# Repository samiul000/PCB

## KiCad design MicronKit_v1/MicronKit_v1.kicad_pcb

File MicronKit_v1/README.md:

<div align="center">
<h1>MicronKit : PIC32 based MCU Program Flasher (V1.0)</h1>

</div>

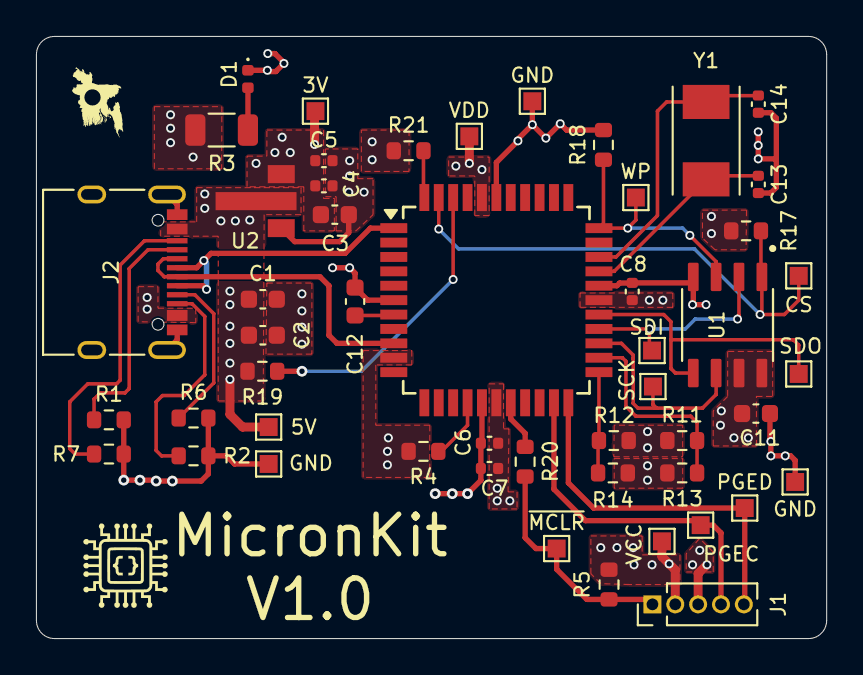
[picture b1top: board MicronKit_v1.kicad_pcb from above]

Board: 4 copper layers, 43.9 x 33.4 mm, 49 parts (0 on the bottom side), 27 nets.

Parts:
3V, 5V: TestPoint; TestPoint_Pad_1.0x1.0mm
C1: 0.22uF; C_0603_1608Metric
C2, C3, C11: 1uF; C_0603_1608Metric
C4, C6, C7, C8: 0.1uF; C_0402_1005Metric
C5: 10nF; C_0402_1005Metric
C12: 10uF; C_0603_1608Metric
C13, C14: 22pF; C_0402_1005Metric
CS: TestPoint; TestPoint_Pad_1.0x1.0mm
D1: LED; LED_0402_1005Metric
GND: TestPoint; TestPoint_Pad_1.0x1.0mm
GND#2, GND#3: TestPoint; TestPoint_Pad_1.0x1.0mm
J1: Conn_01x05_Pin; PinHeader_1x05_P1.27mm_Vertical
J2: USB_C_Receptacle_USB2.0_16P; USB_C_Receptacle_XKB_U262-16XN-4BVC11
PGEC: TestPoint; TestPoint_Pad_1.0x1.0mm
PGED: TestPoint; TestPoint_Pad_1.0x1.0mm
R1, R2, R6, R7: 5.1K; R_0603_1608Metric
R3: 1K; R_1206_3216Metric
R4, R5, R12, R17, R21: 10K; R_0603_1608Metric
R11: 3.92K; R_0603_1608Metric
R13, R14: 2.21K; R_0603_1608Metric
R18: 2.2K; R_0603_1608Metric
R19: 100; R_0603_1608Metric
R20: 470; R_0603_1608Metric
SCK: TestPoint; TestPoint_Pad_1.0x1.0mm
SDI: TestPoint; TestPoint_Pad_1.0x1.0mm
SDO: TestPoint; TestPoint_Pad_1.0x1.0mm
U1: 25LC256; 25LC256-I_SN
U2: MCP1700T-3302E_MB
U3: PIC32MX250F128D-IPT; TQFP-44_10x10mm_P0.8mm
VCC: TestPoint; TestPoint_Pad_1.0x1.0mm
VDD: TestPoint; TestPoint_Pad_1.0x1.0mm
WP: TestPoint; TestPoint_Pad_1.0x1.0mm
Y1: 12 MHz; Crystal_SMD_Abracon_ABM7-2Pin_6.0x3.5mm

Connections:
+3.3V: 3V.1, C3.1, C4.1, C5.1, C6.1, C7.1, C8.1, C11.1, J1.2, R3.1, R4.1, R5.1, R11.1, R12.1, R17.1, R21.1, U1.7 (~HOLD), U1.8 (VDD), U2.3 (VO), U3.10 (VUSB3V3), U3.17 (AVDD), U3.28 (VDD), U3.40 (VDD), VCC.1, VDD.1
+5V: 5V.1, C1.1, C2.1, J2.A4 (VBUS), J2.A9 (VBUS), J2.B4 (VBUS), J2.B9 (VBUS), R19.2, U2.2 (VI)
A5: J2.A5 (CC1), R1.1
A8: J2.A8 (SBU1), R6.1
B5: J2.B5 (CC2), R2.1
B8: J2.B8 (SBU2), R7.1
D_Minus: J2.A7 (D-), J2.B7 (D-), U3.9 (RB11)
D_Plus: J2.A6 (D+), J2.B6 (D+), U3.1 (RB9)
GND: C1.2, C2.2, C3.2, C4.2, C5.2, C6.2, C7.2, C8.2, C11.2, C12.1, C13.2, C14.2, D1.1 (K), GND.1, GND#2.1, GND#3.1, J1.3, J2.A1 (GND), J2.A12 (GND), J2.B1 (GND), J2.B12 (GND), J2.S1 (SHIELD), R1.2, R2.2, R6.2, R7.2, R13.2, R14.2, R18.2, U1.4 (GND), U2.1 (GND), U3.6 (VSS), U3.16 (AVSS), U3.29 (VSS), U3.39 (VSS)
unnamed: D1.2 (A), R3.2
unnamed: C13.1, U3.30 (RA2), Y1.1
unnamed: C14.1, U3.31 (RA3), Y1.2
unnamed: R21.2, U3.44 (RB8)
unnamed: R19.1, U3.42 (VBUS)
unnamed: C12.2, U3.7 (VCAP)
unnamed: R20.2, U3.18 (~MCLR)
PGEC: J1.4, PGEC.1, U3.21 (RB0)
PGED: J1.5, PGED.1, U3.22 (RB1)
Power_Good: R4.2, U3.15 (RB15)
UTIL_CS: CS.1, R17.2, U1.1 (~CS), U3.43 (RB7)
UTIL_SCK: SCK.1, U1.6 (SCK), U3.25 (RC0)
UTIL_SDI: SDI.1, U1.2 (SDO), U3.26 (RC1)
UTIL_SDO: SDO.1, U1.5 (SDI), U3.27 (RC2)
UTIL_WP: R18.1, U1.3 (~WP), U3.33 (RB4), WP.1
VDD_SENSE: R11.2, R13.1, U3.24 (RB3)
VPP_SENSE: R12.2, R14.1, U3.23 (RB2)
~MCLR: J1.1, R5.2, R20.1

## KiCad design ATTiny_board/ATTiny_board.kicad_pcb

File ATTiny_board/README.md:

<div align="center">
<h1>Tiny Board: ATTiny87-M based dev board</h1>

</div>

---

## Hardware
- Flash Program Memory:	8 KB
- SRAM (RAM):	512 bytes
- EEPROM:	512 bytes
- Maximum Clock Speed:	16 MHz
- CPU Architecture:	AVR 8-bit RISC
- GPIO Pins: 10
- I2C: 1
- SPI: 1
- Dimension: 26.75mm x 28.025mm

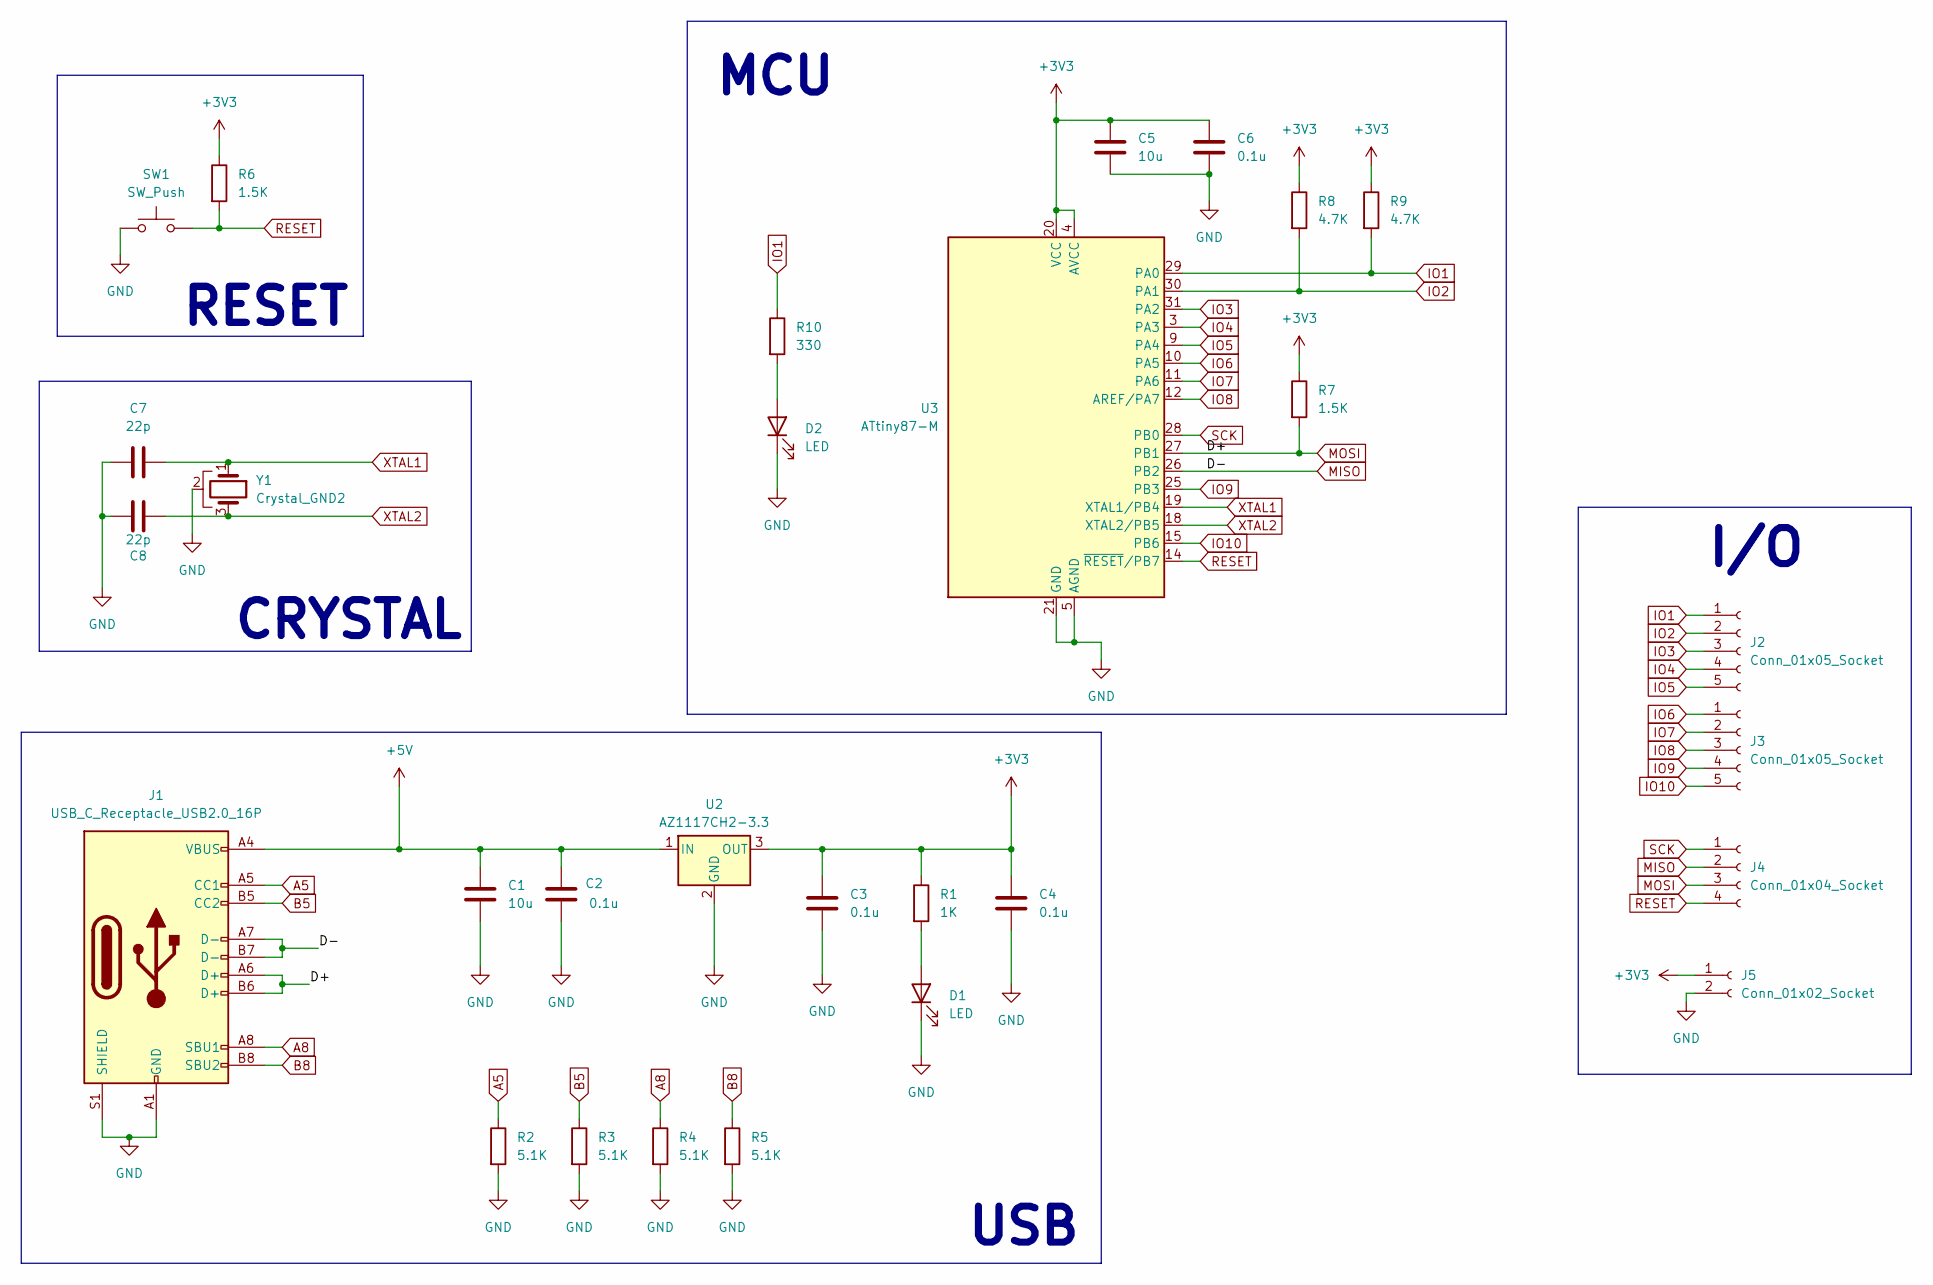
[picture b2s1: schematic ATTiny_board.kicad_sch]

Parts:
C1, C5: 10u; C_0603_1608Metric
C2, C3, C4, C6: 0.1u; C_0603_1608Metric
C7, C8: 22p; C_0402_1005Metric
D1, D2: LED; LED_0603_1608Metric
J1: USB_C_Receptacle_USB2.0_16P; USB_C_Receptacle_GCT_USB4105-xx-A_16P_TopMnt_Horizontal
J2, J3: Conn_01x05_Socket; PinSocket_1x05_P2.54mm_Vertical
J4: Conn_01x04_Socket; PinSocket_1x04_P2.54mm_Vertical
J5: Conn_01x02_Socket; PinSocket_1x02_P2.54mm_Vertical
R1: 1K; R_0603_1608Metric
R2, R3, R4, R5: 5.1K; R_0603_1608Metric
R6, R7: 1.5K; R_0603_1608Metric
R8, R9: 4.7K; R_0603_1608Metric
R10: 330; R_0603_1608Metric
SW1: SW_Push; SW_Push_1P1T_NO_CK_KMR2
U2: AZ1117CH2-3.3; SOT-223-3_TabPin2
U3: ATtiny87-M; QFN-32-1EP_5x5mm_P0.5mm_EP3.1x3.1mm
Y1: Crystal_GND2; XTAL_C3E-12.000-18-3030-X-R

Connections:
+3V3: C3.1, C4.1, C5.1, C6.1, J5.1, R1.1, R6.1, R7.1, R8.1, R9.1, U2.3 (OUT), U3.4 (AVCC), U3.20 (VCC)
+5V: C1.1, C2.1, J1.A4 (VBUS), J1.A9 (VBUS), J1.B4 (VBUS), J1.B9 (VBUS), U2.1 (IN)
A5: J1.A5 (CC1), R2.1
A8: J1.A8 (SBU1), R4.1
B5: J1.B5 (CC2), R3.1
B8: J1.B8 (SBU2), R5.1
GND: C1.2, C2.2, C3.2, C4.2, C5.2, C6.2, C7.1, C8.2, D1.1 (K), D2.1 (K), J1.A1 (GND), J1.A12 (GND), J1.B1 (GND), J1.B12 (GND), J1.S1 (SHIELD), J5.2, R2.2, R3.2, R4.2, R5.2, SW1.1, U2.2 (GND), U3.5 (AGND), U3.21 (GND), U3.33 (GND), Y1.2
IO1: J2.1, R9.2, R10.1, U3.29 (PA0)
IO2: J2.2, R8.2, U3.30 (PA1)
IO3: J2.3, U3.31 (PA2)
IO4: J2.4, U3.3 (PA3)
IO5: J2.5, U3.9 (PA4)
IO6: J3.1, U3.10 (PA5)
IO7: J3.2, U3.11 (PA6)
IO8: J3.3, U3.12 (AREF/PA7)
IO9: J3.4, U3.25 (PB3)
IO10: J3.5, U3.15 (PB6)
MISO: J1.A7 (D-), J1.B7 (D-), J4.2, U3.26 (PB2)
MOSI: J1.A6 (D+), J1.B6 (D+), J4.3, R7.2, U3.27 (PB1)
unnamed: D1.2 (A), R1.2
unnamed: D2.2 (A), R10.2
RESET: J4.4, R6.2, SW1.2, U3.14 (~RESET/PB7)
SCK: J4.1, U3.28 (PB0)
XTAL1: C7.2, U3.19 (XTAL1/PB4), Y1.1
XTAL2: C8.1, U3.18 (XTAL2/PB5), Y1.3

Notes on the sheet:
I/O
CRYSTAL
USB
MCU
RESET

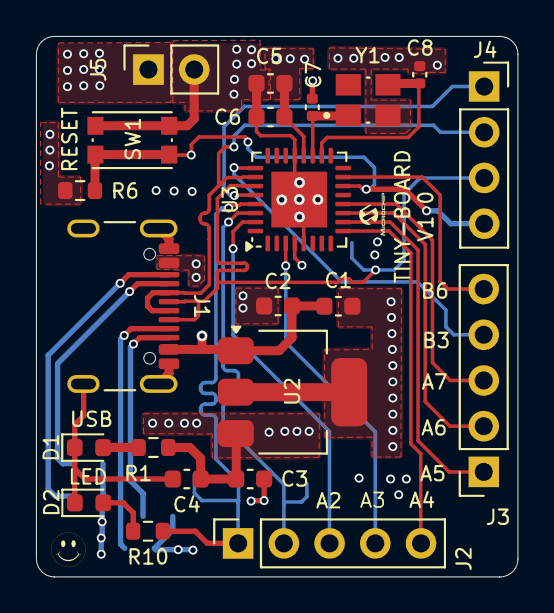
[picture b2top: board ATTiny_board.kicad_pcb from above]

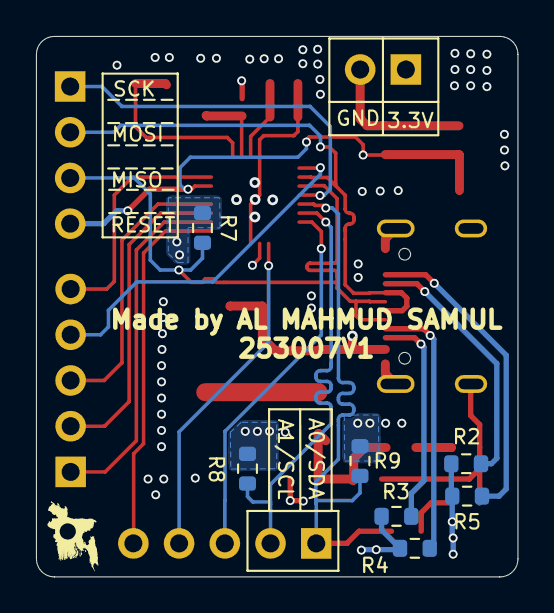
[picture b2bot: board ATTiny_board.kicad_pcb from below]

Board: 4 copper layers, 26.8 x 30.0 mm, 29 parts (7 on the bottom side), 25 nets.

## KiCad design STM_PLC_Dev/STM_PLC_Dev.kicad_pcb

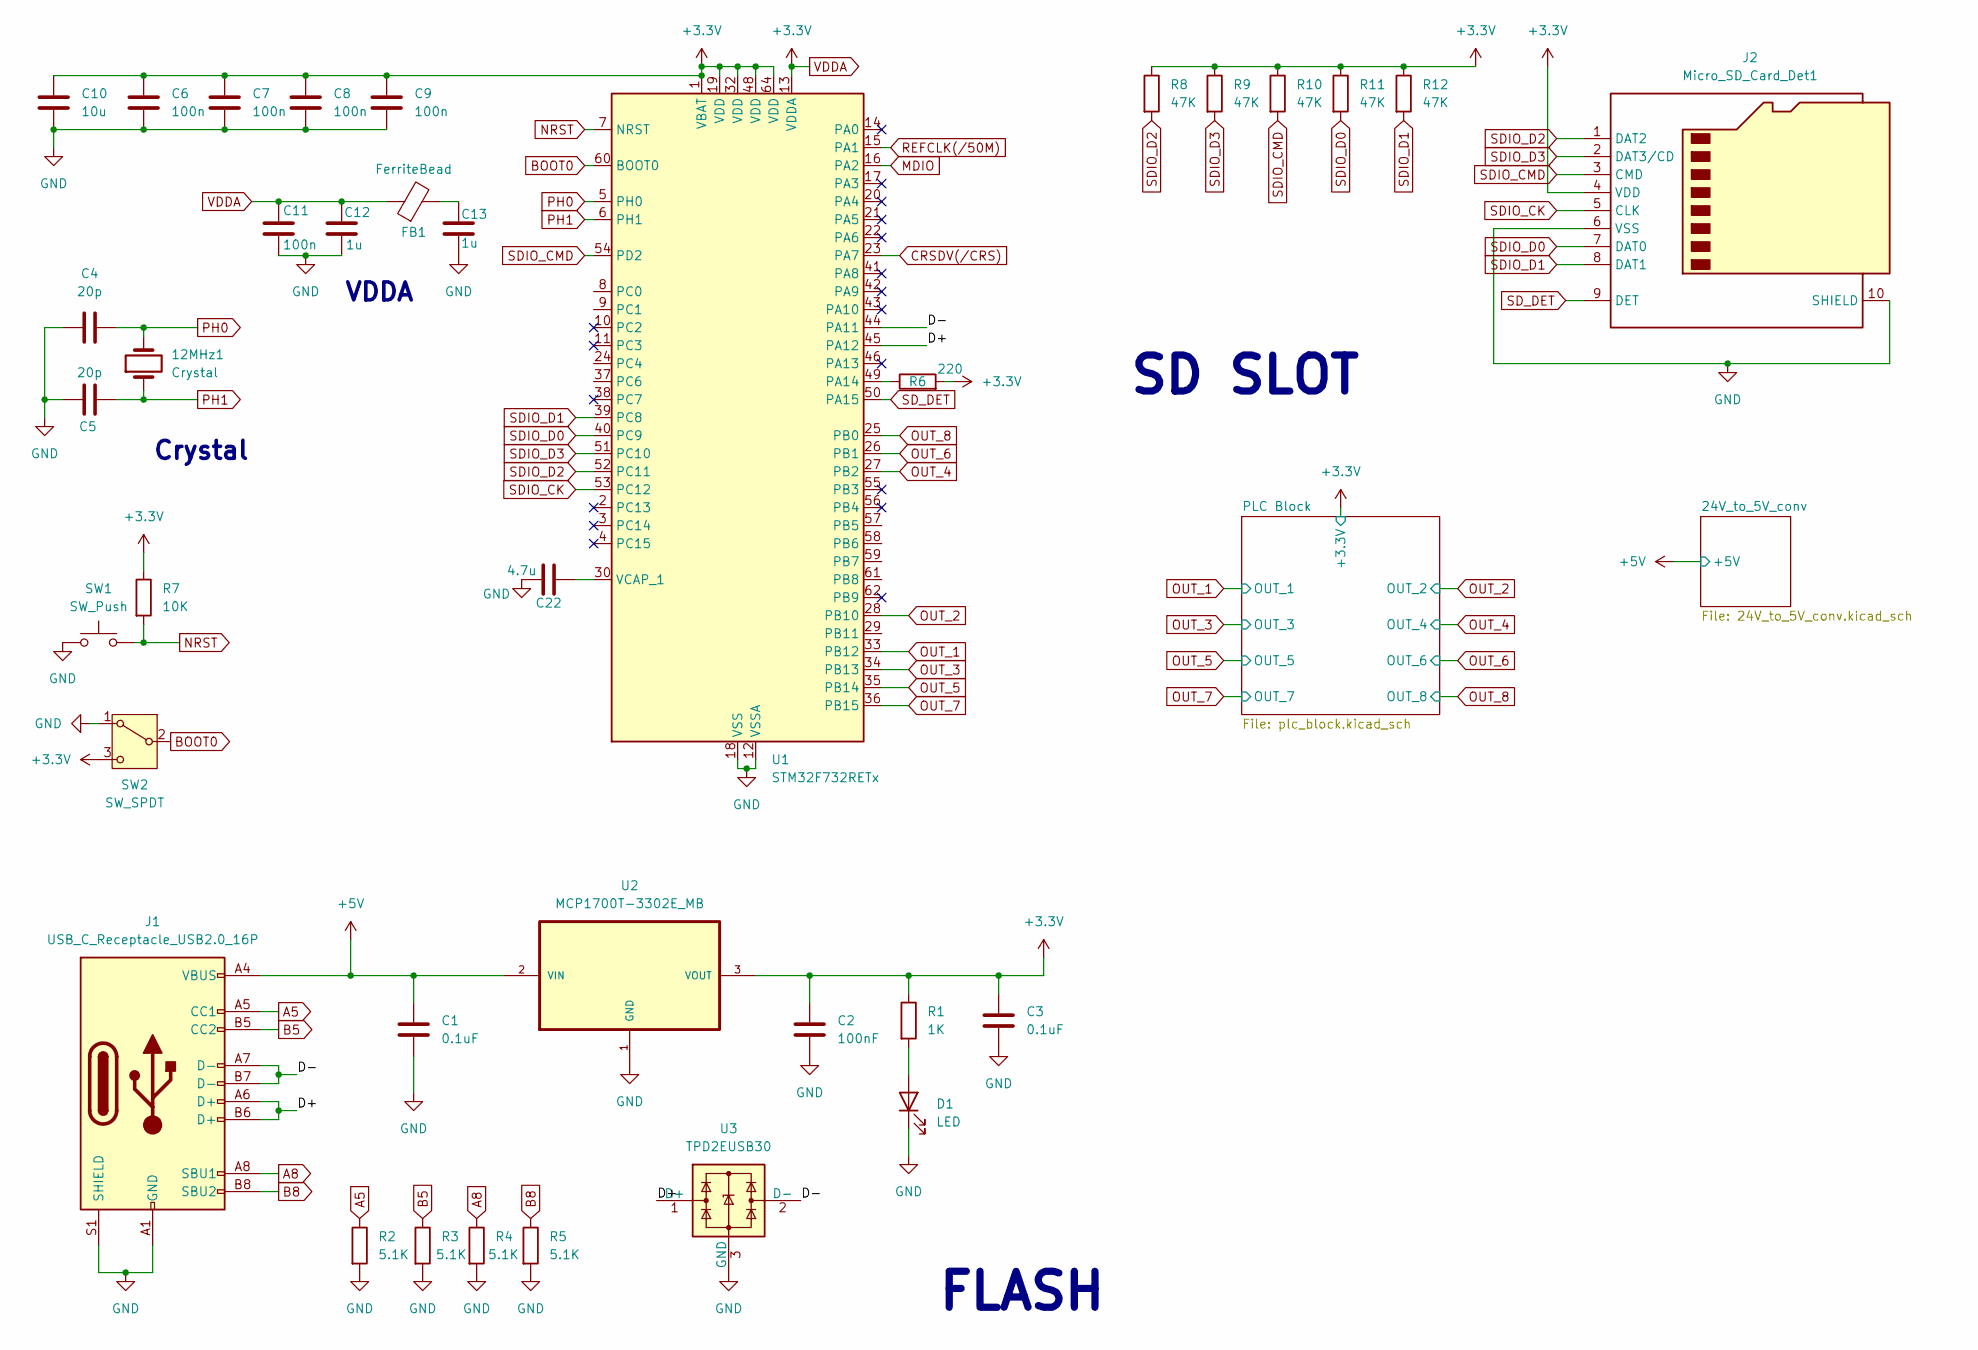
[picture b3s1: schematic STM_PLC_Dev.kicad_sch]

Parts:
12MHz1: Crystal; XTAL_HC49P488W46L1150T500H350
C1, C3: 0.1uF; C_0603_1608Metric
C2: 100nF; C_0603_1608Metric
C4, C5: 20p; C_0603_1608Metric
C6, C7, C8, C9, C11: 100n; C_0603_1608Metric
C10: 10u; C_0603_1608Metric
C12, C13: 1u; C_0603_1608Metric
C22: 4.7u; C_0603_1608Metric
D1: LED; LED_0805_2012Metric
FB1: FerriteBead; LairdTech_28C0236-0JW-10
J1: USB_C_Receptacle_USB2.0_16P; USB_C_Receptacle_G-Switch_GT-USB-7010ASV
J2: Micro_SD_Card_Det1; microSD_HC_Hirose_DM3AT-SF-PEJM5
R1: 1K; R_0805_2012Metric
R2, R3, R4, R5: 5.1K; R_0805_2012Metric
R6: 220; R_0603_1608Metric
R7: 10K; R_0805_2012Metric
R8, R9, R10, R11, R12: 47K; R_0805_2012Metric
SW1: SW_Push; SW_PUSH-12mm_Wuerth-430476085716
SW2: SW_SPDT; SW_E-Switch_EG1224_SPDT_Angled
U1: STM32F732RETx; LQFP-64_10x10mm_P0.5mm
U2: MCP1700T-3302E_MB
U3: TPD2EUSB30; Texas_DRT-3

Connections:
+5V: C1.1, J1.A4 (VBUS), J1.A9 (VBUS), J1.B4 (VBUS), J1.B9 (VBUS), U2.2 (VIN); also elsewhere on the board
/D+: J1.A6 (D+), J1.B6 (D+), U1.45 (PA12), U3.1 (D+)
/D-: J1.A7 (D-), J1.B7 (D-), U1.44 (PA11), U3.2 (D-)
A5: J1.A5 (CC1), R2.1
A8: J1.A8 (SBU1), R4.1
B5: J1.B5 (CC2), R3.1
B8: J1.B8 (SBU2), R5.1
BOOT0: SW2.2 (B), U1.60 (BOOT0)
CRSDV(/CRS): U1.23 (PA7)
GND: C1.2, C2.2, C3.2, C4.1, C5.1, C6.2, C7.2, C8.2, C9.2, C10.2, C11.2, C12.2, C13.2, C22.1, D1.1 (K), J1.A1 (GND), J1.A12 (GND), J1.B1 (GND), J1.B12 (GND), J1.S1 (SHIELD), J2.6 (VSS), J2.10 (SHIELD), R2.2, R3.2, R4.2, R5.2, SW1.1, SW2.1 (A), U1.12 (VSSA), U1.18 (VSS), U1.31 (VSS), U1.47 (VSS), U1.63 (VSS), U2.1 (GND), U3.3 (GND); also elsewhere on the board
MDIO: U1.16 (PA2)
NRST: R7.2, SW1.2, U1.7 (NRST)
unnamed: C13.1, FB1.2
unnamed: D1.2 (A), R1.2
unnamed: R6.1, U1.49 (PA14)
unnamed: C22.2, U1.30 (VCAP_1)
OUT_1: U1.33 (PB12); also elsewhere on the board
OUT_2: U1.28 (PB10); also elsewhere on the board
OUT_3: U1.34 (PB13); also elsewhere on the board
OUT_4: U1.27 (PB2); also elsewhere on the board
OUT_5: U1.35 (PB14); also elsewhere on the board
OUT_6: U1.26 (PB1); also elsewhere on the board
OUT_7: U1.36 (PB15); also elsewhere on the board
OUT_8: U1.25 (PB0); also elsewhere on the board
PH0: 12MHz1.2, C4.2, U1.5 (PH0)
PH1: 12MHz1.1, C5.2, U1.6 (PH1)
REFCLK(/50M): U1.15 (PA1)
SDIO_CK: J2.5 (CLK), U1.53 (PC12)
SDIO_CMD: J2.3 (CMD), R10.2, U1.54 (PD2)
SDIO_D0: J2.7 (DAT0), R11.2, U1.40 (PC9)
SDIO_D1: J2.8 (DAT1), R12.2, U1.39 (PC8)
SDIO_D2: J2.1 (DAT2), R8.2, U1.52 (PC11)
SDIO_D3: J2.2 (DAT3/CD), R9.2, U1.51 (PC10)
SD_DET: J2.9 (DET), U1.50 (PA15)
VDDA: C2.1, C3.1, C6.1, C7.1, C8.1, C9.1, C10.1, C11.1, C12.1, FB1.1, J2.4 (VDD), R1.1, R6.2, R7.1, R8.1, R9.1, R10.1, R11.1, R12.1, SW2.3 (C), U1.1 (VBAT), U1.13 (VDDA), U1.19 (VDD), U1.32 (VDD), U1.48 (VDD), U1.64 (VDD), U2.3 (VOUT); also elsewhere on the board

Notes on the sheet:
FLASH
Crystal
SD SLOT
VDDA

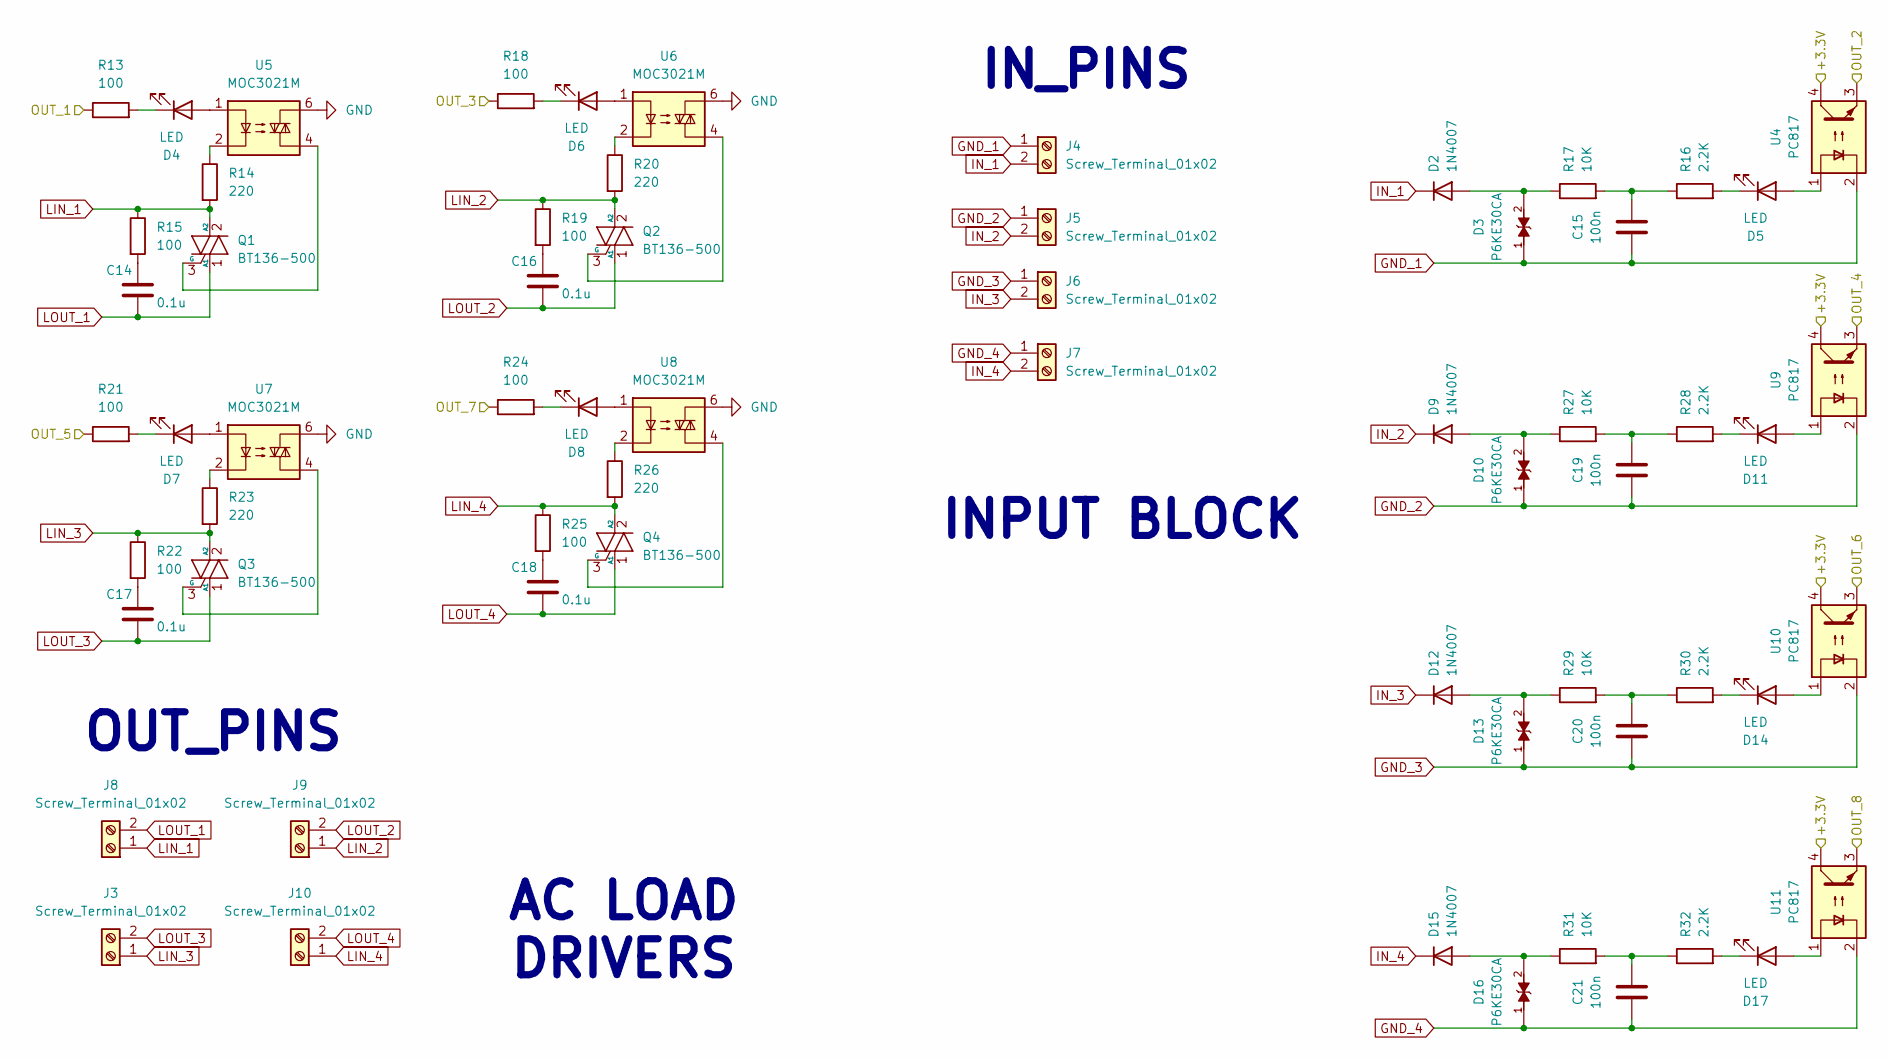
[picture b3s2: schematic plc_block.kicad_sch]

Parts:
C14, C16, C17, C18: 0.1u; C_Rect_L18.0mm_W8.0mm_P15.00mm_FKS3_FKP3
C15, C19, C20, C21: 100n; C_0805_2012Metric
D2, D9, D12, D15: 1N4007; D_DO-41_SOD81_P10.16mm_Horizontal
D3, D10, D13, D16: P6KE30CA; DIOAD1300W80L670D310; PARTREV O2109; DigiKey_Part_Number P6KE30CALFTR-ND
D4, D5, D6, D7, D8, D11, D14, D17: LED; LED_D3.0mm
J3, J4, J5, J6, J7, J8, J9, J10: Screw_Terminal_01x02; CUI_TB004-508-02BE
Q1, Q2, Q3, Q4: BT136-500; TO-220-3_Vertical
R13, R18, R21, R24: 100; R_Axial_DIN0207_L6.3mm_D2.5mm_P10.16mm_Horizontal
R14, R20, R23, R26: 220; R_Axial_DIN0207_L6.3mm_D2.5mm_P10.16mm_Horizontal
R15, R19, R22, R25: 100; R_Axial_DIN0309_L9.0mm_D3.2mm_P20.32mm_Horizontal
R16, R28, R30, R32: 2.2K; R_Axial_DIN0207_L6.3mm_D2.5mm_P10.16mm_Horizontal
R17, R27, R29, R31: 10K; R_Axial_DIN0207_L6.3mm_D2.5mm_P10.16mm_Horizontal
U4, U9, U10, U11: PC817; DIP-4_W7.62mm
U5, U6, U7, U8: MOC3021M; DIP762W48P254L889H508Q6

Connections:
GND: U5.6, U6.6, U7.6, U8.6; also elsewhere on the board
GND_1: C15.1, D3.1, J4.1, U4.2
GND_2: C19.1, D10.1, J5.1, U9.2
GND_3: C20.1, D13.1, J6.1, U10.2
GND_4: C21.1, D16.1, J7.1, U11.2
IN_1: D2.1 (K), J4.2
IN_2: D9.1 (K), J5.2
IN_3: D12.1 (K), J6.2
IN_4: D15.1 (K), J7.2
LIN_1: J8.1, Q1.2 (A2), R14.2, R15.1
LIN_2: J9.1, Q2.2 (A2), R19.1, R20.2
LIN_3: J3.1, Q3.2 (A2), R22.1, R23.2
LIN_4: J10.1, Q4.2 (A2), R25.1, R26.2
LOUT_1: C14.2, J8.2, Q1.1 (A1)
LOUT_2: C16.2, J9.2, Q2.1 (A1)
LOUT_3: C17.2, J3.2, Q3.1 (A1)
LOUT_4: C18.2, J10.2, Q4.1 (A1)
unnamed: C14.1, R15.2
unnamed: C15.2, R16.1, R17.2
unnamed: C16.1, R19.2
unnamed: C17.1, R22.2
unnamed: C18.1, R25.2
unnamed: C19.2, R27.2, R28.1
unnamed: C20.2, R29.2, R30.1
unnamed: C21.2, R31.2, R32.1
unnamed: D2.2 (A), D3.2, R17.1
unnamed: D4.2 (A), U5.1
unnamed: D4.1 (K), R13.2
unnamed: D5.2 (A), U4.1
unnamed: D5.1 (K), R16.2
unnamed: D6.2 (A), U6.1
unnamed: D6.1 (K), R18.2
unnamed: D7.2 (A), U7.1
unnamed: D7.1 (K), R21.2
unnamed: D8.2 (A), U8.1
unnamed: D8.1 (K), R24.2
unnamed: D9.2 (A), D10.2, R27.1
unnamed: D11.2 (A), U9.1
unnamed: D11.1 (K), R28.2
unnamed: D12.2 (A), D13.2, R29.1
unnamed: D14.2 (A), U10.1
unnamed: D14.1 (K), R30.2
unnamed: D15.2 (A), D16.2, R31.1
unnamed: D17.2 (A), U11.1
unnamed: D17.1 (K), R32.2
unnamed: Q1.3 (G), U5.4
unnamed: Q2.3 (G), U6.4
unnamed: Q3.3 (G), U7.4
unnamed: Q4.3 (G), U8.4
unnamed: R14.1, U5.2
unnamed: R20.1, U6.2
unnamed: R23.1, U7.2
unnamed: R26.1, U8.2
OUT_1: R13.1; also elsewhere on the board
OUT_2: U4.3; also elsewhere on the board
OUT_3: R18.1; also elsewhere on the board
OUT_4: U9.3; also elsewhere on the board
OUT_5: R21.1; also elsewhere on the board
OUT_6: U10.3; also elsewhere on the board
OUT_7: R24.1; also elsewhere on the board
OUT_8: U11.3; also elsewhere on the board
VDDA: U4.4, U9.4, U10.4, U11.4; also elsewhere on the board

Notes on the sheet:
AC LOAD DRIVERS
OUT_PINS
INPUT BLOCK
IN_PINS

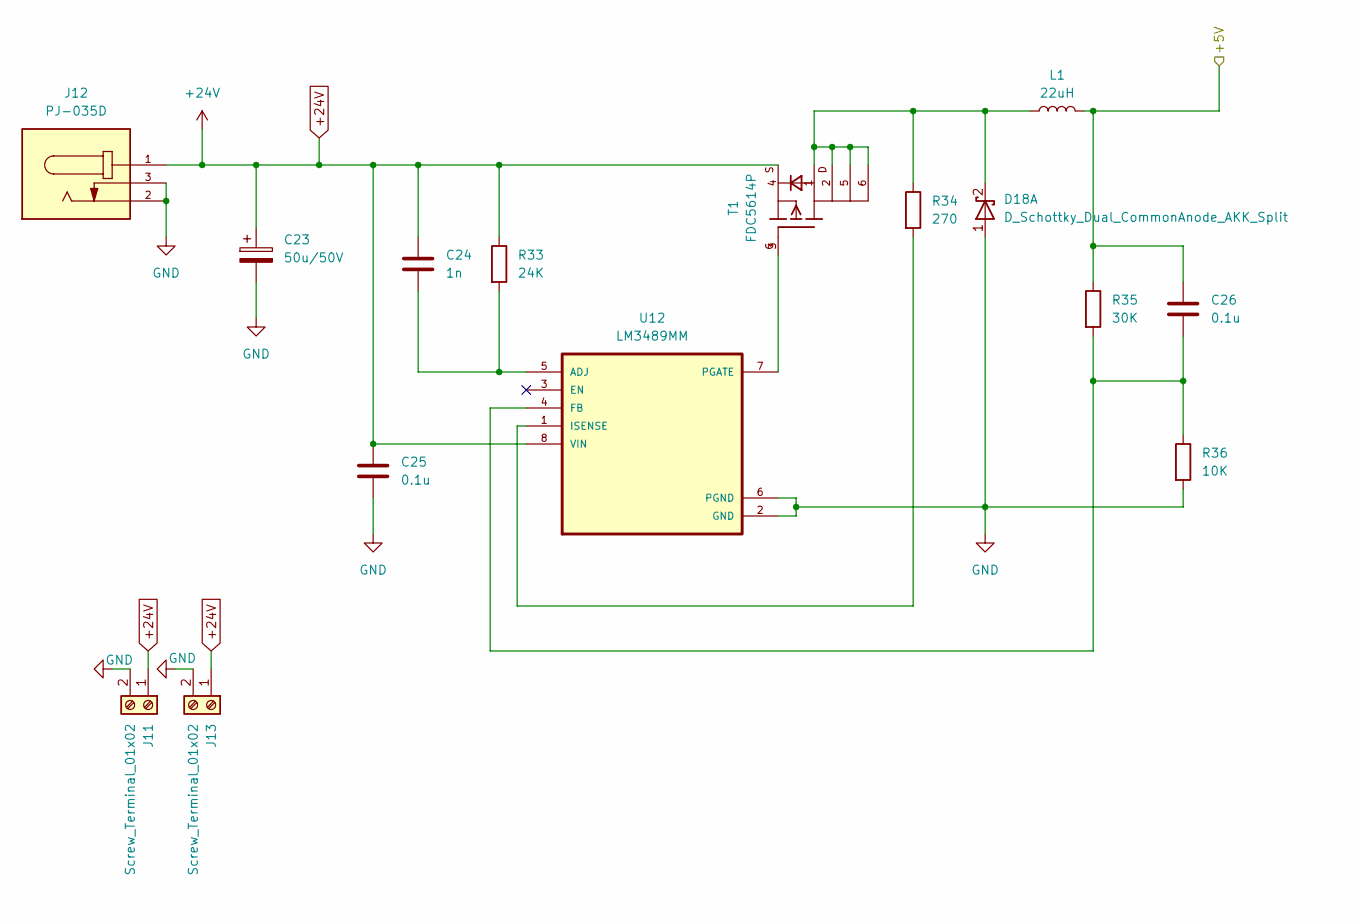
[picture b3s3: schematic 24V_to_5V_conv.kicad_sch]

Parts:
C23: 50u/50V; C_0603_1608Metric
C24: 1n; C_0402_1005Metric
C25, C26: 0.1u; C_0603_1608Metric
D18: D_Schottky_Dual_CommonAnode_AKK_Split; D_0603_1608Metric
J11, J13: Screw_Terminal_01x02; CUI_TB004-508-02BE
J12: PJ-035D; CUI_PJ-035D; PARTREV 1.05
L1: 22uH; L_0603_1608Metric
R33: 24K; R_0603_1608Metric
R34: 270; R_0603_1608Metric
R35: 30K; R_0603_1608Metric
R36: 10K; R_0603_1608Metric
T1: FDC5614P; SOT23-6
U12: LM3489MM; SOP65P490X110-8N

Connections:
+5V: C26.1, L1.2, R35.1; also elsewhere on the board
+24V: C23.1, C24.1, C25.1, J11.1, J12.1, J13.1, R33.1, T1.4, U12.8 (VIN)
GND: C23.2, C25.2, D18.1 (A), J11.2, J12.2, J12.3, J13.2, R36.2, U12.2 (GND), U12.6 (PGND); also elsewhere on the board
unnamed: D18.2 (K), L1.1, R34.1, T1.1, T1.2, T1.5, T1.6
unnamed: C24.2, R33.2, U12.5 (ADJ)
unnamed: C26.2, R35.2, R36.1, U12.4 (FB)
unnamed: R34.2, U12.1 (ISENSE)
unnamed: T1.3, U12.7 (PGATE)

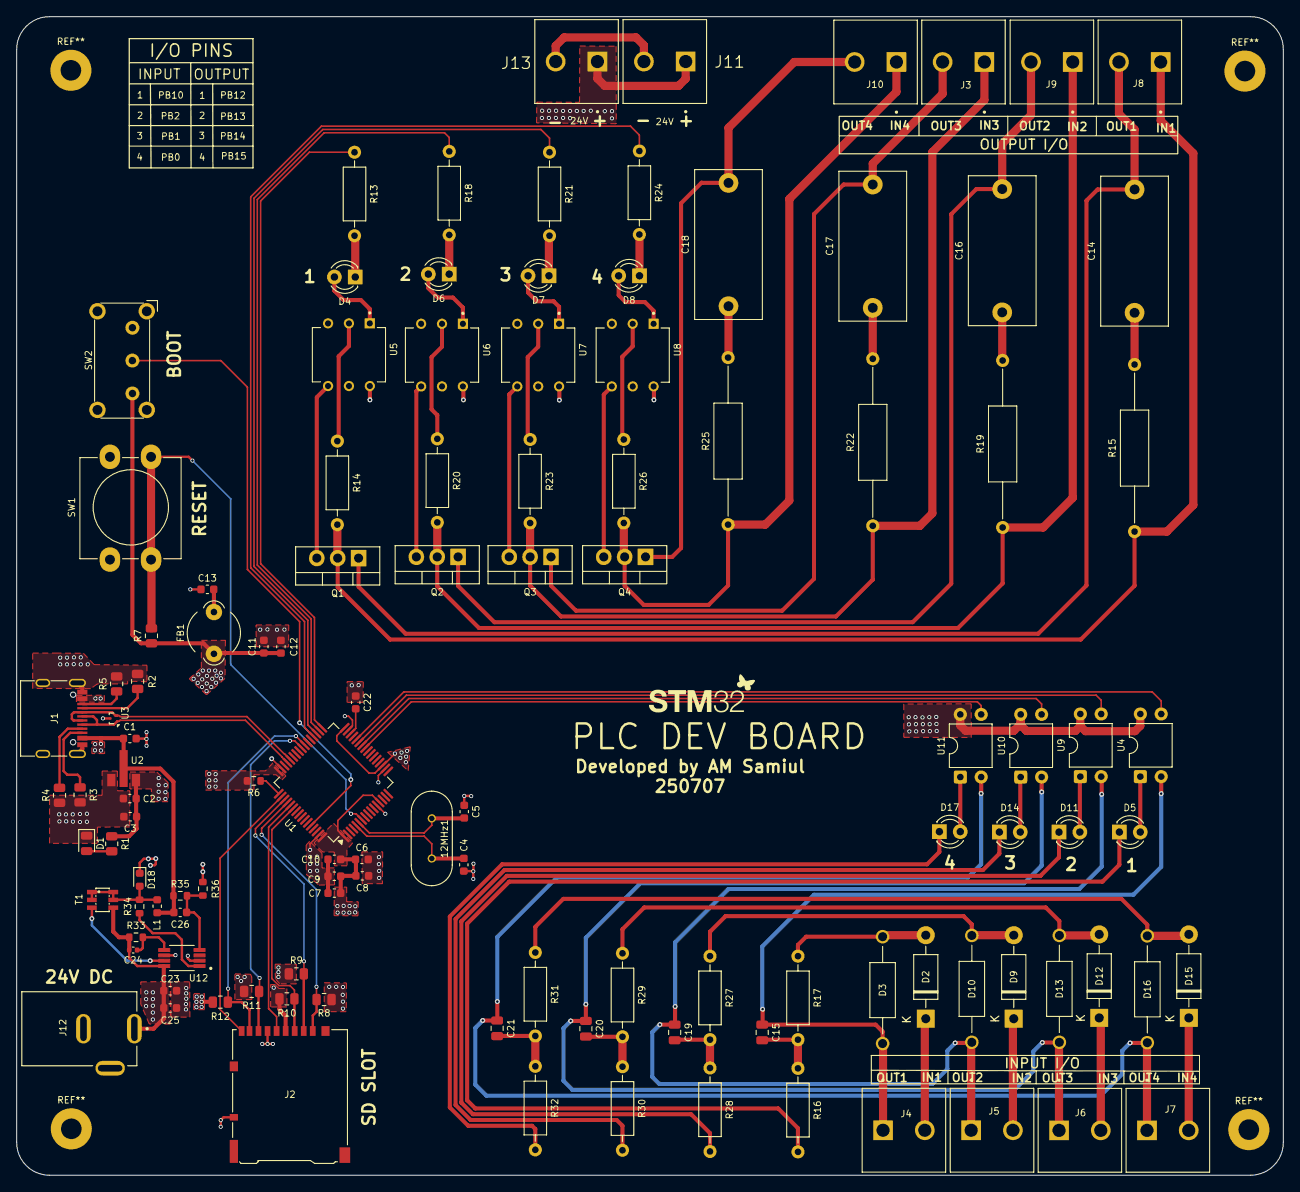
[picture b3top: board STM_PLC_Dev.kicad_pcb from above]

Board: 4 copper layers, 154.1 x 140.9 mm, 115 parts (0 on the bottom side), 90 nets.

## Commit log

2025-07-07 Rename STM_PLC_Dev.csv to STM_PLC_Dev.csv
2025-07-07 Rename STM_PLC_Dev.png to STM_PLC_Dev.png
2025-07-07 Update and rename fp-lib-table to fp-lib-table
2025-07-07 Update and rename sym-lib-table to sym-lib-table
2026-06-03 Create Tiny_Board
2026-06-03 Fix formatting issues in README.md
2026-06-03 Create README.md for MicroKit project
    Add initial README for MicroKit project with title and image.
2026-06-03 Fix image filename in README.md
2026-06-03 Fix typo in project name from 'MicroKit' to 'MicronKit'
